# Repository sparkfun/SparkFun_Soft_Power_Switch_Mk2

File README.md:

SparkFun Soft Power Switch - JST 2mm
===================================================

[*SparkFun Soft Power Switch - JST 2mm (PRT-26993)*](https://www.sparkfun.com/products/26993)

The Soft Power Switch - JST 2mm is a passive, hard on/off switch with software feedback and control. In other words, it's like the on/off switch on a laptop. A simple press will turn the system on. Another press can (with MCU intervention) turn off the system. And if things go really wrong, pressing and holding the button for ~7 seconds will force a power-down. If you're building something with an enclosed battery and need a good power button, this is the board you need.

The [Mk1 Soft Power Switch](https://www.sparkfun.com/products/17870) is great, but we do see occasional issues caused by component tolerances or the operating temperature. Mk2 is based on an application note by Texas Instruments, and is a completely digital design. It is based around a 74LVC1G175 D-type flip-flop - remember those?! - and is insensitive to temperature and component variation. It also includes improvements like: an over-current self-resetting 2A fuse; input and output LEDs. This version has JST 2mm battery connectors.

The PUSH pin can act as an output to a microcontroller indicating the state of the power button (high = not pressed, low = user is pressing power button). This can be used as an input to your firmware to begin to shut down before power is lost. PUSH is an open-drain output and requires a pull-up. Alternatively, the OFF pin can be driven **high** by the system forcing fast power off via software. (For Mk1, the Fast Off pin was driven **low**.)

The most common use case is something like this:

* Microcontroller begins running code and checks to see if the power button is still being pressed for X milliseconds.
* If not, it's just a tap, go back to sleep.
* If yes, power up and run normal program.

Later...

* User presses power button in normal program
* If power button is pressed for <X milliseconds, it's just a tap, ignore.
* If power button is pressed for >X milliseconds, it's time to power down.

The wake-up and power-down times can be tweaked for your own user experience but we found 500ms for power up and 2s for power down work really well.

If needed, pads are provided for a larger, external button.

The Soft Power Switch supports battery charging. If the target device has onboard LiPo charging, current can be passed back through the switch circuit and charge the battery.

<b>Heads up!</b> The Soft Power Switch - JST 2mm works up to 5.5V only. (Mk1 is good up to 12V.)

Pros:

* Very low µA quiescent current
* Hard override power down in case your microcontroller loses its mind
* PUSH and OFF pins can be connected to a microcontroller
* Supports battery charging

Cons:

* Limited to 2A continuous, 4A peak (fuse protected)
* No AC loads

Features
-------------------
* Input voltage: 5.5V maximum, 1.8V minimum
    * Typically ~3.7V from a single cell LiPo Battery
* Maximum current draw: 2A continuous, 4A peak (fuse protected)
* SIL2308 N&P-Channel MOSFET
    * 70mΩ (0.070 Ohm) typical P-Channel on-resistance
* Very low quiescent current: <1µA @ 3.75V, with VIN LED disabled
* 2x 2-Pin JST Right-Angle Connectors
    * VIN
    * VOUT
* Supports battery charging
* Built-in momentary push button
  * Hard override: push and hold the button for ~10 seconds
* Breakout PTH:
  * GND, VIN, VOUT
  * BTN: if desired, connect an external button between BTN and GND
  * PUSH: open-drain output, requires pull-up, low indicates button is pushed
  * OFF: drive high to turn the output off
* LEDs: VIN and VOUT (can be disabled if desired)
* Jumpers
  * Input power LED
  * Output power LED
* Dimensions: 1.0in. x 1.0in. (25.4mm x 25.4mm)
* Weight: 3.10g

Repository Contents
-------------------

* **.github/workflows** - YAML files used for GitHub Actions and GitHub Pages/mkdocs
* **/Examples** - Example sketches demonstrating how to read and control the switch
* **/Hardware** - KiCad design files (kicad_pro, .kicad_pcb, .kicad_sch)
  * **/Production** - Production panel files
* **/docs** - Online documentation files
  * **/assets** - Folder containing all the file assets used for product documentation
    *  **/3d_model** - Exported 3D models from KiCad
    * **/board_files** - Copy of design files used for product documentation
    * **/component_documentation** - Datasheets and manuals for hardware components
    * **/img** - Images for product documentation
  * **/github** - Files stating how to contribute and filing issues used for product documentation
  * **/javascript** - Folder containing custom javascript used for product documentation
  * **/stylesheet** - Folder containing CSS files used for product documentation
* **/overrides** - Customization files used for product documentation
  * **/.icons** - Icons used for GitHub used for product documentation
  * **./partials** - Used for product documentation
* **LICENSE.md** contains the license information

Documentation
--------------
* **[Hookup Guide](https://docs.sparkfun.com/SparkFun_Soft_Power_Switch_Mk2)** - Basic hookup guide for the Soft Power Switch - JST 2mm.

Product Versions
----------------
* [PRT-26993](https://www.sparkfun.com/products/26993) - SparkFun Red Release Soft Power Switch - JST 2mm
* [SPX-25365](https://www.sparkfun.com/products/25365) - Original SparkX Release Soft Power Switch Mk2 - JST 2mm
* [SPX-17870](https://www.sparkfun.com/products/17870) - Original SparkX Release Mk1

Version History
---------------
* v1.0 - SparkFun Soft Power Switch - JST 2mm (PRT-26993)
* v01 - Original SparkX Soft Power Switch MK2 - JST 2mm (SPX-25365)
* v1.0 - Original SparkX Soft Power Switch Mk1 (SPX-17870)

License Information
-------------------

This product is _**open source**_!

Please review the LICENSE.md file for license information.

If you have any questions or concerns on licensing, please contact technical support on our [SparkFun forums](https://forum.sparkfun.com/viewforum.php?f=123).

Distributed as-is; no warranty is given.

- Your friends at SparkFun.

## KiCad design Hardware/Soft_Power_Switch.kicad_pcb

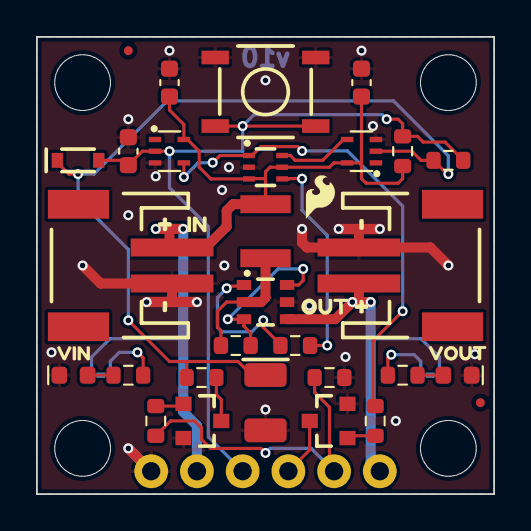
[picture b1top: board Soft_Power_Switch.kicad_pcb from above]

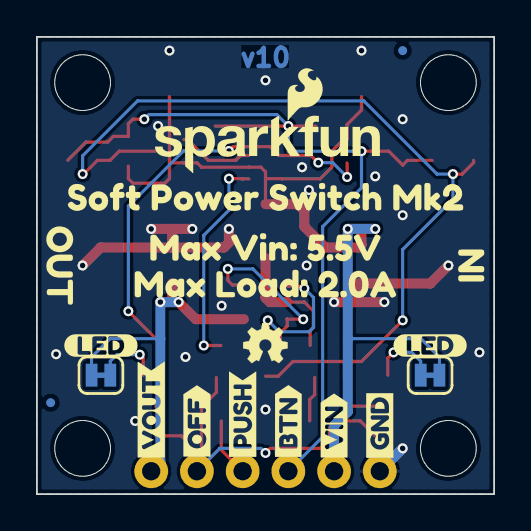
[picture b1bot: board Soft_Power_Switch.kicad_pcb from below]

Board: 2 copper layers, 25.4 x 25.4 mm, 61 parts (18 on the bottom side), 20 nets.

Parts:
C1, C3: 1.0uF; C_0603_1608Metric
C2: 47uF; EIA-3528
C4: 0.1uF; C_0603_1608Metric
D1: BAS16J; SOD-323
D2, D3: Red; LED_0603_1608Metric_Red
F1: 6V/2.0A/4.0A; 1210
FID1, FID2, FID3, FID4: Fiducial_0.5mm; Fiducial_0.5mm_Mask1mm
G3: OSHW_Logo; Creative_Commons_License
J1, J2: JST_2mm_LiPo; JST_SMD_2.0mm-2
J3: Conn_01x06; 1x06
JP1, JP2: Jumper_2_NC_Trace
Q1, Q2: BSS138; SOT23-3
Q3: SIL2308; SOT23-6-Tight
R1, R6, R8, R9: 1k; R_0603_1608Metric
R2: 200k; R_0603_1608Metric
R3, R4, R7: 10k; R_0603_1608Metric
R5: 100; R_0603_1608Metric
R10: 100k; R_0603_1608Metric
Ref**: Val**; OSHW_Logo_2.5mm
ST1, ST2, ST3, ST4: Standoff
SW1: SMD_5.2x5.2mm_h2.5mm; Push_SMD_5.2x5.2mm_h2.5mm
U2: SN74LVC1G14DCK; SOT-353
U3: SN74LVC1G17DCK; SOT-353
U4: SN74LVC1G175DCK; SOT-323
kibuzzard-65F04F60, kibuzzard-65F04F60#2: G***; kibuzzard-65F04F60
kibuzzard-65F04FCA, kibuzzard-65F04FCA#2: G***; kibuzzard-65F04FCA
kibuzzard-65F053F1: G***; kibuzzard-65F053F1
kibuzzard-65F054C3, kibuzzard-65F054C3#2: G***; kibuzzard-65F054C3
kibuzzard-65F056B4: G***; kibuzzard-65F056B4
kibuzzard-65F056D8: G***; kibuzzard-65F056D8
kibuzzard-65F056F7: G***; kibuzzard-65F056F7
kibuzzard-65F174FD: G***; kibuzzard-65F174FD
kibuzzard-65F0543A: G***; kibuzzard-65F0543A
kibuzzard-65F0634B: G***; kibuzzard-65F0634B
kibuzzard-65F0636B: G***; kibuzzard-65F0636B
kibuzzard-65F1758C: G***; kibuzzard-65F1758C
kibuzzard-65F05416: G***; kibuzzard-65F05416
kibuzzard-65F05472: G***; kibuzzard-65F05472
kibuzzard-65F05495: G***; kibuzzard-65F05495
kibuzzard-65F05604: G***; kibuzzard-65F05604
kibuzzard-65F05628: G***; kibuzzard-65F05628
kibuzzard-65F05644: G***; kibuzzard-65F05644

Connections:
BTN: C1.1, D1.A, J3.4, R1.2, R2.2, SW1.2, U2.2
EN: R9.2, U4.4 (Q)
GND: C1.2, C2.2, C3.2, C4.2, D2.1 (K), D3.1 (K), J1.1 (-), J2.1 (-), J3.6, Q1.2 (S), Q2.2 (S), Q3.5 (S), R7.2, SW1.1, U2.3 (GND), U3.3 (GND), U4.2 (GND)
unnamed: C2.1, D1.C, R2.1, R5.1, U3.2
unnamed: D2.2 (A), R3.2
unnamed: D3.2 (A), R4.2
unnamed: JP1.1 (A), R3.1
unnamed: JP2.1 (A), R4.1
unnamed: Q1.3 (D), R5.2
unnamed: Q1.1 (G), R6.1
unnamed: Q2.1 (G), R8.2
unnamed: Q3.3 (G), Q3.6 (D), R10.1
unnamed: Q3.1 (G), R9.1
unnamed: F1.1, Q3.2 (1), R10.2
unnamed: R8.1, U2.4, U4.1 (CLK)
unnamed: U3.4, U4.6 (~CLR)
OFF: J3.2, R6.2, R7.1
PUSH: J3.3, Q2.3 (D)
VIN: C3.1, C4.1, F1.2, J1.2 (+), J3.5, JP1.2 (B), R1.1, U2.5 (VCC), U3.5 (VCC), U4.3 (D), U4.5 (VCC)
VOUT: J2.2 (+), J3.1, JP2.2 (B), Q3.4 (D)

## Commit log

2024-10-01 Update 3D models
2024-10-24 Initial Push GitHub Pages
2024-10-25 Add images and more content to tutorial
2024-11-01 Update products, fix minor typos, add notes
2024-11-01 Update Product Name
2024-11-05 Add Hardware Hookup Pictures, Fix Spelling
2024-11-07 Adjust Required Materials
2024-11-08 Minor Update to Hardware Overview and Hookup
2024-11-08 Deployed a1387e7 with MkDocs version: 1.6.1
2024-11-14 Add 3D Models
2024-11-15 Remove STL File
2024-12-05 Deployed fe2565f with MkDocs version: 1.6.1
2025-01-03 Add panel. Single PCB gerbers moved into Production_Single_PCB
2025-01-03 Deployed 53e6f26 with MkDocs version: 1.6.1
2025-09-11 Remove git-authors
2026-06-03 Deployed 137e85c with MkDocs version: 1.6.1

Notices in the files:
parts and their libraries:
Released under the Creative Commons Attribution Share-Alike 4.0 License
https://creativecommons.org/licenses/by-sa/4.0
